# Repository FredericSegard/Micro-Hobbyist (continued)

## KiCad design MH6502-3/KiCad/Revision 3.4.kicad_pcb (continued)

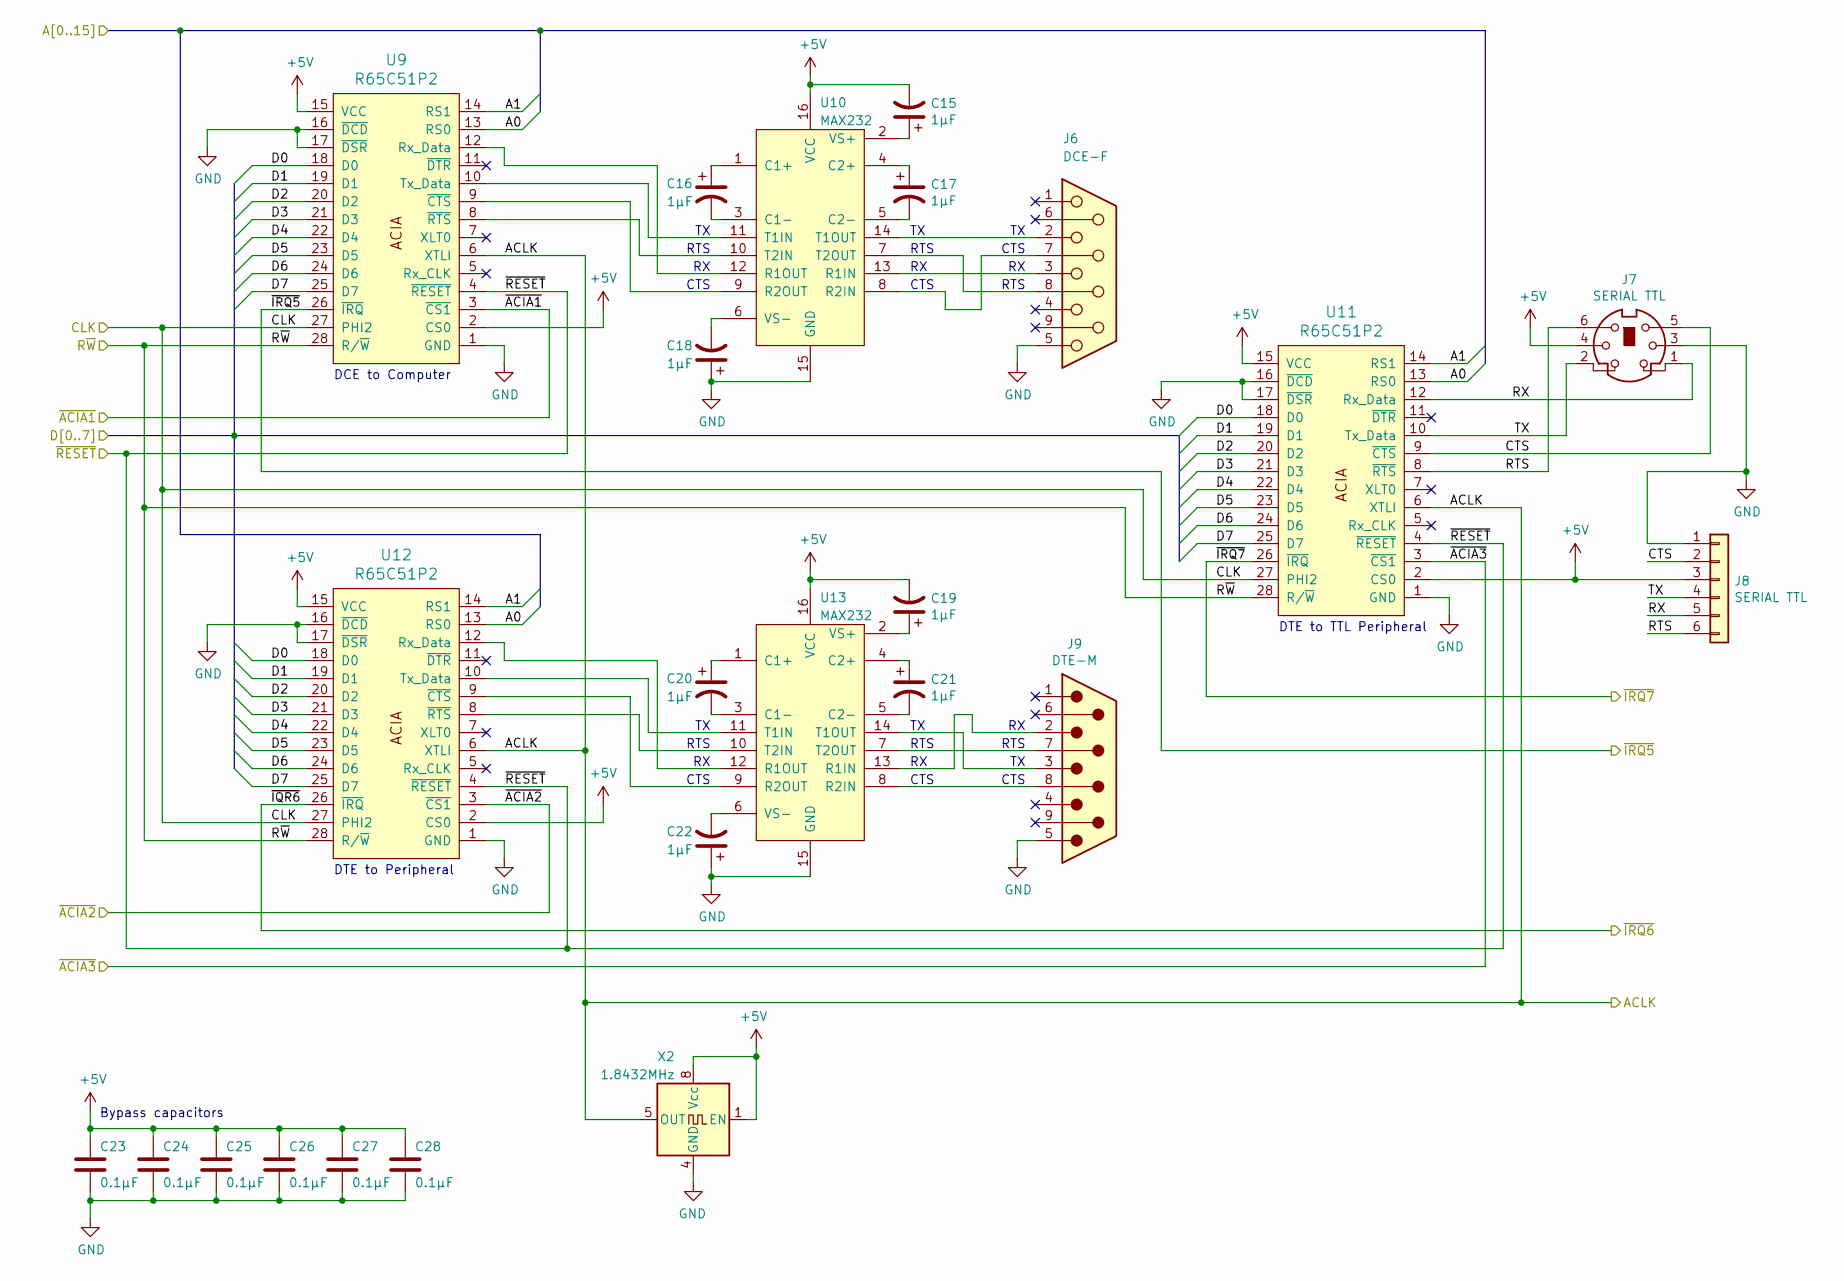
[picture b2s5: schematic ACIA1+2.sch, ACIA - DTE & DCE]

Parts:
C15, C16, C17, C18, C19, C20, C21, C22: 1µF; C_Disc_D3.0mm_W1.6mm_P2.50mm
C23, C24, C25, C26, C27, C28: 0.1µF; C_Disc_D3.0mm_W1.6mm_P2.50mm
J6: DCE-F; DSUB-9_Female_Horizontal_P2.77x2.84mm_EdgePinOffset7.70mm_H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
J7: SERIAL TTL; Mini-DIN_6p
J8: SERIAL TTL; PinHeader_1x06_P2.54mm_Vertical
J9: DTE-M; DSUB-9_Male_Horizontal_P2.77x2.84mm_EdgePinOffset7.70mm_Hou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
U9, U11, U12: R65C51P2; DIP-28_W15.24mm_Socket
U10, U13: MAX232; DIP-16_W7.62mm_Socket
X2: 1.8432MHz; Oscillator_DIP-8

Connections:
+5V: C15.2, C19.2, C23.1, C24.1, C25.1, C26.1, C27.1, C28.1, J7.4, J8.3, U9.2 (CS0), U9.15 (VCC), U10.16 (VCC), U11.2 (CS0), U11.15 (VCC), U12.2 (CS0), U12.15 (VCC), U13.16 (VCC), X2.1 (EN), X2.8 (Vcc); also elsewhere on the board
/ACIA 1, 2 & 3/A0: U9.13 (RS0), U11.13 (RS0), U12.13 (RS0); also elsewhere on the board
/ACIA 1, 2 & 3/A1: U9.14 (RS1), U11.14 (RS1), U12.14 (RS1); also elsewhere on the board
/ACIA 1, 2 & 3/CTS: J7.5, J8.2, U11.9 (~CTS)
/ACIA 1, 2 & 3/D0: U9.18 (D0), U11.18 (D0), U12.18 (D0); also elsewhere on the board
/ACIA 1, 2 & 3/D1: U9.19 (D1), U11.19 (D1), U12.19 (D1); also elsewhere on the board
/ACIA 1, 2 & 3/D2: U9.20 (D2), U11.20 (D2), U12.20 (D2); also elsewhere on the board
/ACIA 1, 2 & 3/D3: U9.21 (D3), U11.21 (D3), U12.21 (D3); also elsewhere on the board
/ACIA 1, 2 & 3/D4: U9.22 (D4), U11.22 (D4), U12.22 (D4); also elsewhere on the board
/ACIA 1, 2 & 3/D5: U9.23 (D5), U11.23 (D5), U12.23 (D5); also elsewhere on the board
/ACIA 1, 2 & 3/D6: U9.24 (D6), U11.24 (D6), U12.24 (D6); also elsewhere on the board
/ACIA 1, 2 & 3/D7: U9.25 (D7), U11.25 (D7), U12.25 (D7); also elsewhere on the board
/ACIA 1, 2 & 3/RTS: J7.6, J8.6, U11.8 (~RTS)
/ACIA 1, 2 & 3/RX: J7.1, J8.5, U11.12 (Rx_Data)
/ACIA 1, 2 & 3/TX: J7.2, J8.4, U11.10 (Tx_Data)
/ACLK: U9.6 (XTLI), U11.6 (XTLI), U12.6 (XTLI), X2.5 (OUT); also elsewhere on the board
/CLK: U9.27 (PHI2), U11.27 (PHI2), U12.27 (PHI2); also elsewhere on the board
/R~W: U9.28 (R/~W), U11.28 (R/~W), U12.28 (R/~W); also elsewhere on the board
/~ACIA1: U9.3 (~CS1); also elsewhere on the board
/~ACIA2: U12.3 (~CS1); also elsewhere on the board
/~ACIA3: U11.3 (~CS1); also elsewhere on the board
/~IRQ5: U9.26 (~IRQ); also elsewhere on the board
/~IRQ6: U12.26 (~IRQ); also elsewhere on the board
/~IRQ7: U11.26 (~IRQ); also elsewhere on the board
/~RESET: U9.4 (~RESET), U11.4 (~RESET), U12.4 (~RESET); also elsewhere on the board
GND: C18.1, C22.1, C23.2, C24.2, C25.2, C26.2, C27.2, C28.2, J6.5, J7.3, J8.1, J9.5, U9.1 (GND), U9.16 (~DCD), U9.17 (~DSR), U10.15 (GND), U11.1 (GND), U11.16 (~DCD), U11.17 (~DSR), U12.1 (GND), U12.16 (~DCD), U12.17 (~DSR), U13.15 (GND), X2.4 (GND); also elsewhere on the board
unnamed: C15.1, U10.2 (VS+)
unnamed: C16.1, U10.1 (C1+)
unnamed: C16.2, U10.3 (C1-)
unnamed: C17.1, U10.4 (C2+)
unnamed: C17.2, U10.5 (C2-)
unnamed: C18.2, U10.6 (VS-)
unnamed: C19.1, U13.2 (VS+)
unnamed: C20.1, U13.1 (C1+)
unnamed: C20.2, U13.3 (C1-)
unnamed: C21.1, U13.4 (C2+)
unnamed: C21.2, U13.5 (C2-)
unnamed: C22.2, U13.6 (VS-)
unnamed: J6.2, U10.14 (T1OUT)
unnamed: J6.3, U10.13 (R1IN)
unnamed: J6.7, U10.8 (R2IN)
unnamed: J6.8, U10.7 (T2OUT)
unnamed: J9.2, U13.13 (R1IN)
unnamed: J9.3, U13.14 (T1OUT)
unnamed: J9.7, U13.7 (T2OUT)
unnamed: J9.8, U13.8 (R2IN)
unnamed: U9.9 (~CTS), U10.9 (R2OUT)
unnamed: U9.8 (~RTS), U10.10 (T2IN)
unnamed: U9.10 (Tx_Data), U10.11 (T1IN)
unnamed: U9.12 (Rx_Data), U10.12 (R1OUT)
unnamed: U12.8 (~RTS), U13.10 (T2IN)
unnamed: U12.9 (~CTS), U13.9 (R2OUT)
unnamed: U12.10 (Tx_Data), U13.11 (T1IN)
unnamed: U12.12 (Rx_Data), U13.12 (R1OUT)

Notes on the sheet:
RTS
CTS
DCE to Computer
DTE to Peripheral
Bypass capacitors
DTE to TTL Peripheral

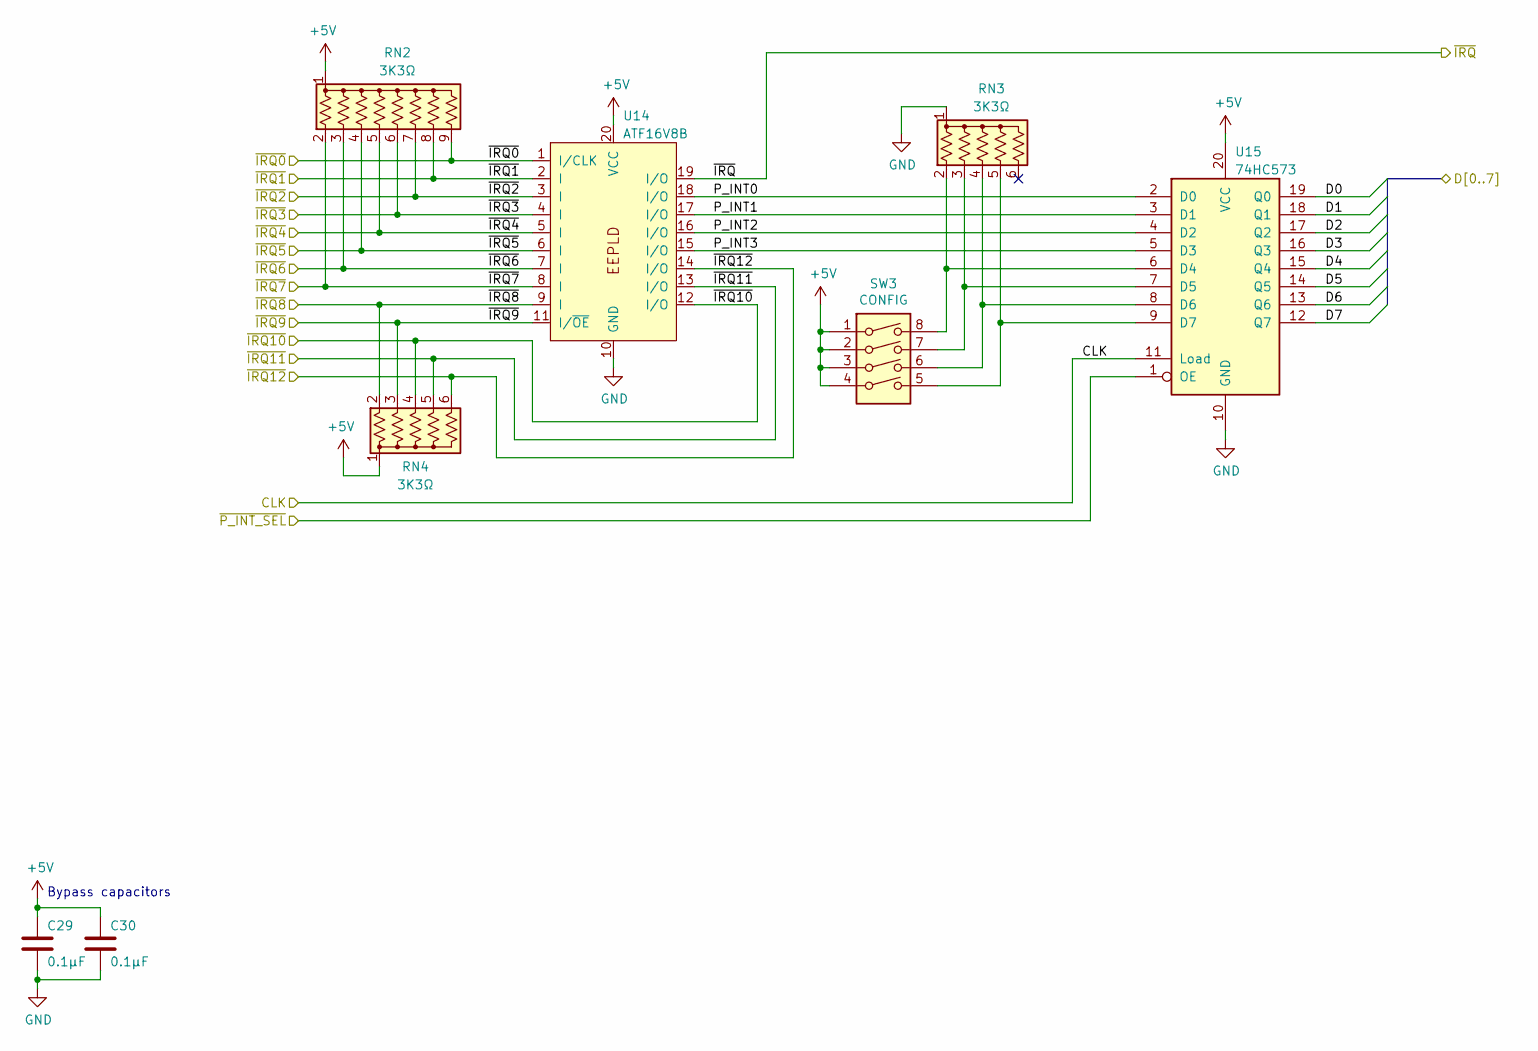
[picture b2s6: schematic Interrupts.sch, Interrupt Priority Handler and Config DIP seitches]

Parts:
C29, C30: 0.1µF; C_Disc_D3.0mm_W1.6mm_P2.50mm
RN2: 3K3Ω; R_Array_SIP9
RN3, RN4: 3K3Ω; R_Array_SIP6
SW3: CONFIG; SW_DIP_SPSTx04_Slide_9.78x12.34mm_W7.62mm_P2.54mm
U14: ATF16V8B; DIP-20_W7.62mm_Socket
U15: 74HC573; DIP-20_W7.62mm_Socket

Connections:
+5V: C29.1, C30.1, RN2.1 (common), RN4.1 (common), SW3.1, SW3.2, SW3.3, SW3.4, U14.20 (VCC), U15.20 (VCC); also elsewhere on the board
/ACIA 1, 2 & 3/D0: U15.19 (Q0); also elsewhere on the board
/ACIA 1, 2 & 3/D1: U15.18 (Q1); also elsewhere on the board
/ACIA 1, 2 & 3/D2: U15.17 (Q2); also elsewhere on the board
/ACIA 1, 2 & 3/D3: U15.16 (Q3); also elsewhere on the board
/ACIA 1, 2 & 3/D4: U15.15 (Q4); also elsewhere on the board
/ACIA 1, 2 & 3/D5: U15.14 (Q5); also elsewhere on the board
/ACIA 1, 2 & 3/D6: U15.13 (Q6); also elsewhere on the board
/ACIA 1, 2 & 3/D7: U15.12 (Q7); also elsewhere on the board
/CLK: U15.11 (Load); also elsewhere on the board
/Interrupt Handling/P_INT0: U14.18 (I/O), U15.2 (D0)
/Interrupt Handling/P_INT1: U14.17 (I/O), U15.3 (D1)
/Interrupt Handling/P_INT2: U14.16 (I/O), U15.4 (D2)
/Interrupt Handling/P_INT3: U14.15 (I/O), U15.5 (D3)
/~IRQ: U14.19 (I/O); also elsewhere on the board
/~IRQ0: RN2.9 (R8), U14.1 (I/CLK); also elsewhere on the board
/~IRQ1: RN2.8 (R7), U14.2 (I); also elsewhere on the board
/~IRQ2: RN2.7 (R6), U14.3 (I); also elsewhere on the board
/~IRQ3: RN2.6 (R5), U14.4 (I); also elsewhere on the board
/~IRQ4: RN2.5 (R4), U14.5 (I); also elsewhere on the board
/~IRQ5: RN2.4 (R3), U14.6 (I); also elsewhere on the board
/~IRQ6: RN2.3 (R2), U14.7 (I); also elsewhere on the board
/~IRQ7: RN2.2 (R1), U14.8 (I); also elsewhere on the board
/~IRQ8: RN4.2 (R1), U14.9 (I); also elsewhere on the board
/~IRQ9: RN4.3 (R2), U14.11 (I/~OE); also elsewhere on the board
/~IRQ10: RN4.4 (R3), U14.12 (I/O); also elsewhere on the board
/~IRQ11: RN4.5 (R4), U14.13 (I/O); also elsewhere on the board
/~IRQ12: RN4.6 (R5), U14.14 (I/O); also elsewhere on the board
/~P_INT_SEL: U15.1 (OE); also elsewhere on the board
GND: C29.2, C30.2, RN3.1 (common), U14.10 (GND), U15.10 (GND); also elsewhere on the board
unnamed: RN3.2 (R1), SW3.8, U15.6 (D4)
unnamed: RN3.3 (R2), SW3.7, U15.7 (D5)
unnamed: RN3.4 (R3), SW3.6, U15.8 (D6)
unnamed: RN3.5 (R4), SW3.5, U15.9 (D7)

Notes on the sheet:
Bypass capacitors

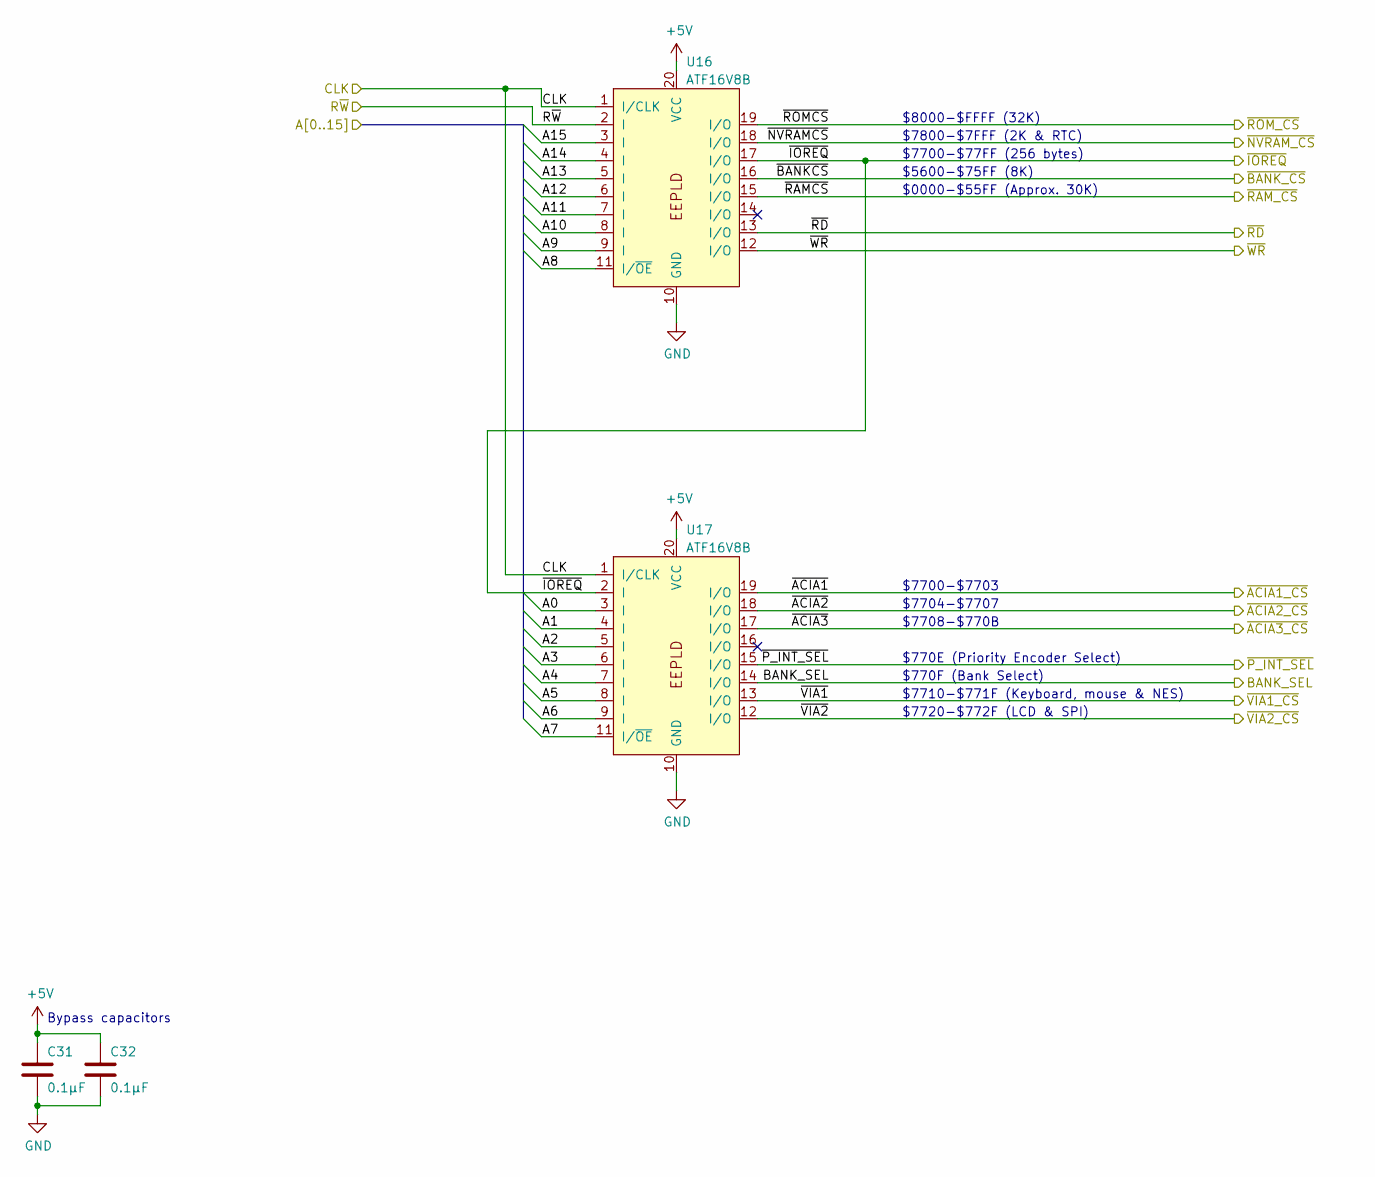
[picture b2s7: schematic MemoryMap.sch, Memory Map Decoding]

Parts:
C31, C32: 0.1µF; C_Disc_D3.0mm_W1.6mm_P2.50mm
U16, U17: ATF16V8B; DIP-20_W7.62mm_Socket

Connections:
+5V: C31.1, C32.1, U16.20 (VCC), U17.20 (VCC); also elsewhere on the board
/ACIA 1, 2 & 3/A0: U17.3 (I); also elsewhere on the board
/ACIA 1, 2 & 3/A1: U17.4 (I); also elsewhere on the board
/BANK_SEL: U17.14 (I/O); also elsewhere on the board
/Bus/A2: U17.5 (I); also elsewhere on the board
/Bus/A3: U17.6 (I); also elsewhere on the board
/Bus/A4: U17.7 (I); also elsewhere on the board
/Bus/A5: U17.8 (I); also elsewhere on the board
/Bus/A6: U17.9 (I); also elsewhere on the board
/Bus/A7: U17.11 (I/~OE); also elsewhere on the board
/Bus/A8: U16.11 (I/~OE); also elsewhere on the board
/Bus/A9: U16.9 (I); also elsewhere on the board
/Bus/A10: U16.8 (I); also elsewhere on the board
/Bus/A11: U16.7 (I); also elsewhere on the board
/Bus/A12: U16.6 (I); also elsewhere on the board
/Bus/A13: U16.5 (I); also elsewhere on the board
/Bus/A14: U16.4 (I); also elsewhere on the board
/Bus/A15: U16.3 (I); also elsewhere on the board
/CLK: U16.1 (I/CLK), U17.1 (I/CLK); also elsewhere on the board
/R~W: U16.2 (I); also elsewhere on the board
/~ACIA1: U17.19 (I/O); also elsewhere on the board
/~ACIA2: U17.18 (I/O); also elsewhere on the board
/~ACIA3: U17.17 (I/O); also elsewhere on the board
/~BANK: U16.16 (I/O); also elsewhere on the board
/~IOREQ: U16.17 (I/O), U17.2 (I); also elsewhere on the board
/~NVRAM: U16.18 (I/O); also elsewhere on the board
/~P_INT_SEL: U17.15 (I/O); also elsewhere on the board
/~RAM: U16.15 (I/O); also elsewhere on the board
/~RD: U16.13 (I/O); also elsewhere on the board
/~ROM: U16.19 (I/O); also elsewhere on the board
/~VIA1: U17.13 (I/O); also elsewhere on the board
/~VIA2: U17.12 (I/O); also elsewhere on the board
/~WR: U16.12 (I/O); also elsewhere on the board
GND: C31.2, C32.2, U16.10 (GND), U17.10 (GND); also elsewhere on the board

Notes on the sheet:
Bypass capacitors
$8000-$FFFF (32K)
$7800-$7FFF (2K & RTC)
$7700-$77FF (256 bytes)
$0000-$55FF (Approx. 30K)
$7700-$7703
$7704-$7707
$7708-$770B
$7710-$771F (Keyboard, mouse & NES)
$5600-$75FF (8K)
$770E (Priority Encoder Select)
$770F (Bank Select)
$7720-$772F (LCD & SPI)

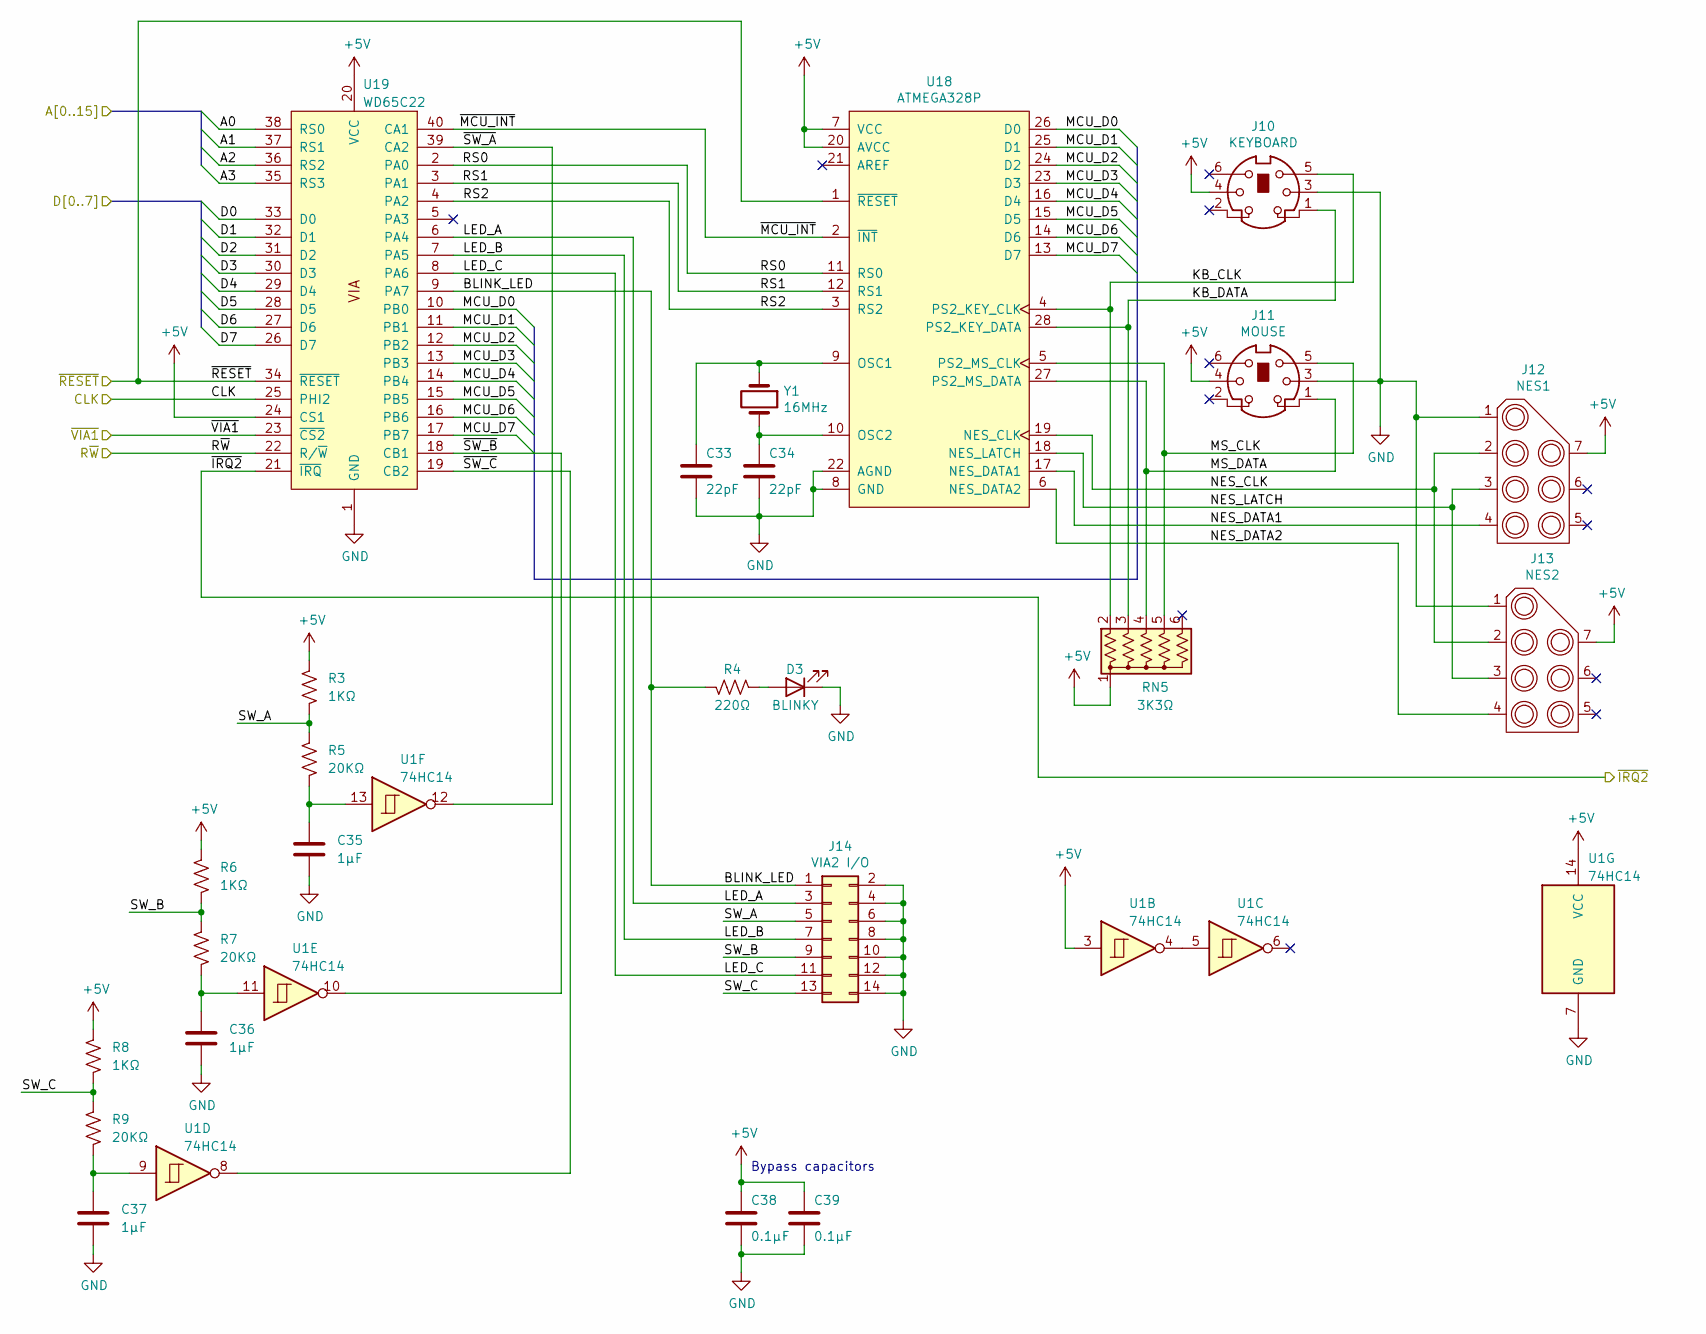
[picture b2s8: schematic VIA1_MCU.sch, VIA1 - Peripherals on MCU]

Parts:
C33, C34: 22pF; C_Disc_D3.0mm_W1.6mm_P2.50mm
C35, C36, C37: 1µF; C_Disc_D3.0mm_W1.6mm_P2.50mm
C38, C39: 0.1µF; C_Disc_D3.0mm_W1.6mm_P2.50mm
D3: BLINKY; LED_D3.0mm
J10: KEYBOARD; Mini-DIN_6p
J11: MOUSE; Mini-DIN_6p
J12: NES1; NES_Connector
J13: NES2; NES_Connector
J14: VIA2 I/O; PinHeader_2x07_P2.54mm_Vertical
R3, R6, R8: 1KΩ; R_Axial_DIN0207_L6.3mm_D2.5mm_P10.16mm_Horizontal
R4: 220Ω; R_Axial_DIN0207_L6.3mm_D2.5mm_P10.16mm_Horizontal
R5, R7, R9: 20KΩ; R_Axial_DIN0207_L6.3mm_D2.5mm_P10.16mm_Horizontal
RN5: 3K3Ω; R_Array_SIP6
U1: 74HC14; DIP-14_W7.62mm_Socket
U18: ATMEGA328P; DIP-28_W7.62mm_Socket
U19: WD65C22; DIP-40_W15.24mm_Socket
Y1: 16MHz; Crystal_HC18-U_Vertical

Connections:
+5V: C38.1, C39.1, J10.4, J11.4, J12.7, J13.7, R3.2, R6.2, R8.2, RN5.1 (common), U1.3, U1.14 (VCC), U18.7 (VCC), U18.20 (AVCC), U19.20 (VCC), U19.24 (CS1); also elsewhere on the board
/ACIA 1, 2 & 3/A0: U19.38 (RS0); also elsewhere on the board
/ACIA 1, 2 & 3/A1: U19.37 (RS1); also elsewhere on the board
/ACIA 1, 2 & 3/D0: U19.33 (D0); also elsewhere on the board
/ACIA 1, 2 & 3/D1: U19.32 (D1); also elsewhere on the board
/ACIA 1, 2 & 3/D2: U19.31 (D2); also elsewhere on the board
/ACIA 1, 2 & 3/D3: U19.30 (D3); also elsewhere on the board
/ACIA 1, 2 & 3/D4: U19.29 (D4); also elsewhere on the board
/ACIA 1, 2 & 3/D5: U19.28 (D5); also elsewhere on the board
/ACIA 1, 2 & 3/D6: U19.27 (D6); also elsewhere on the board
/ACIA 1, 2 & 3/D7: U19.26 (D7); also elsewhere on the board
/Bus/A2: U19.36 (RS2); also elsewhere on the board
/Bus/A3: U19.35 (RS3); also elsewhere on the board
/CLK: U19.25 (PHI2); also elsewhere on the board
/R~W: U19.22 (R/~W); also elsewhere on the board
/VIA1 - Peripherals/BLINK_LED: J14.1, R4.2, U19.9 (PA7)
/VIA1 - Peripherals/KB_CLK: J10.5, RN5.2 (R1), U18.4 (PS2_KEY_CLK)
/VIA1 - Peripherals/KB_DATA: J10.1, RN5.3 (R2), U18.28 (PS2_KEY_DATA)
/VIA1 - Peripherals/LED_A: J14.3, U19.6 (PA4)
/VIA1 - Peripherals/LED_B: J14.7, U19.7 (PA5)
/VIA1 - Peripherals/LED_C: J14.11, U19.8 (PA6)
/VIA1 - Peripherals/MCU_D0: U18.26 (D0), U19.10 (PB0)
/VIA1 - Peripherals/MCU_D1: U18.25 (D1), U19.11 (PB1)
/VIA1 - Peripherals/MCU_D2: U18.24 (D2), U19.12 (PB2)
/VIA1 - Peripherals/MCU_D3: U18.23 (D3), U19.13 (PB3)
/VIA1 - Peripherals/MCU_D4: U18.16 (D4), U19.14 (PB4)
/VIA1 - Peripherals/MCU_D5: U18.15 (D5), U19.15 (PB5)
/VIA1 - Peripherals/MCU_D6: U18.14 (D6), U19.16 (PB6)
/VIA1 - Peripherals/MCU_D7: U18.13 (D7), U19.17 (PB7)
/VIA1 - Peripherals/MS_CLK: J11.5, RN5.5 (R4), U18.5 (PS2_MS_CLK)
/VIA1 - Peripherals/MS_DATA: J11.1, RN5.4 (R3), U18.27 (PS2_MS_DATA)
/VIA1 - Peripherals/NES_CLK: J12.2, J13.2, U18.19 (NES_CLK)
/VIA1 - Peripherals/NES_DATA1: J12.4, U18.17 (NES_DATA1)
/VIA1 - Peripherals/NES_DATA2: J13.4, U18.6 (NES_DATA2)
/VIA1 - Peripherals/NES_LATCH: J12.3, J13.3, U18.18 (NES_LATCH)
/VIA1 - Peripherals/RS0: U18.11 (RS0), U19.2 (PA0)
/VIA1 - Peripherals/RS1: U18.12 (RS1), U19.3 (PA1)
/VIA1 - Peripherals/RS2: U18.3 (RS2), U19.4 (PA2)
/VIA1 - Peripherals/SW_A: J14.5, R3.1, R5.2
/VIA1 - Peripherals/SW_B: J14.9, R6.1, R7.2
/VIA1 - Peripherals/SW_C: J14.13, R8.1, R9.2
/VIA1 - Peripherals/~MCU_INT: U18.2 (~INT), U19.40 (CA1)
/VIA1 - Peripherals/~SW_A: U1.12, U19.39 (CA2)
/VIA1 - Peripherals/~SW_B: U1.10, U19.18 (CB1)
/VIA1 - Peripherals/~SW_C: U1.8, U19.19 (CB2)
/~IRQ2: U19.21 (~IRQ); also elsewhere on the board
/~RESET: U18.1 (~RESET), U19.34 (~RESET); also elsewhere on the board
/~VIA1: U19.23 (~CS2); also elsewhere on the board
GND: C33.2, C34.2, C35.2, C36.2, C37.2, C38.2, C39.2, D3.1 (K), J10.3, J11.3, J12.1, J13.1, J14.2, J14.4, J14.6, J14.8, J14.10, J14.12, J14.14, U1.7 (GND), U18.8 (GND), U18.22 (AGND), U19.1 (GND); also elsewhere on the board
unnamed: C33.1, U18.9 (OSC1), Y1.1
unnamed: C34.1, U18.10 (OSC2), Y1.2
unnamed: C35.1, R5.1, U1.13
unnamed: C36.1, R7.1, U1.11
unnamed: C37.1, R9.1, U1.9
unnamed: D3.2 (A), R4.1
unnamed: U1.4, U1.5

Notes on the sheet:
Bypass capacitors

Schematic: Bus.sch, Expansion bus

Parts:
C40, C41, C42, C43: 10µF; CP_Radial_D6.3mm_P2.50mm
J15: BB BUS; PinHeader_2x20_P2.54mm_Vertical
J16, J18: PWR; PinSocket_2x03_P2.54mm_Vertical
J17: EXT BUS; PinHeader_2x32_P2.54mm_Vertical

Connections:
+5V: C40.1, C41.1, C42.1, C43.1, J15.2, J15.4, J15.37, J15.39, J16.1, J16.3, J16.5, J17.2, J17.4, J17.61, J17.63, J18.1, J18.3, J18.5; also elsewhere on the board
/ACIA 1, 2 & 3/A0: J15.13, J17.13; also elsewhere on the board
/ACIA 1, 2 & 3/A1: J15.14, J17.14; also elsewhere on the board
/ACIA 1, 2 & 3/D0: J15.5, J17.5; also elsewhere on the board
/ACIA 1, 2 & 3/D1: J15.6, J17.6; also elsewhere on the board
/ACIA 1, 2 & 3/D2: J15.7, J17.7; also elsewhere on the board
/ACIA 1, 2 & 3/D3: J15.8, J17.8; also elsewhere on the board
/ACIA 1, 2 & 3/D4: J15.9, J17.9; also elsewhere on the board
/ACIA 1, 2 & 3/D5: J15.10, J17.10; also elsewhere on the board
/ACIA 1, 2 & 3/D6: J15.11, J17.11; also elsewhere on the board
/ACIA 1, 2 & 3/D7: J15.12, J17.12; also elsewhere on the board
/ACLK: J15.33, J17.47; also elsewhere on the board
/BE: J17.51; also elsewhere on the board
/Bus/A2: J15.15, J17.15; also elsewhere on the board
/Bus/A3: J15.16, J17.16; also elsewhere on the board
/Bus/A4: J15.17, J17.17; also elsewhere on the board
/Bus/A5: J15.18, J17.18; also elsewhere on the board
/Bus/A6: J15.19, J17.19; also elsewhere on the board
/Bus/A7: J15.20, J17.20; also elsewhere on the board
/Bus/A8: J17.21; also elsewhere on the board
/Bus/A9: J17.22; also elsewhere on the board
/Bus/A10: J17.23; also elsewhere on the board
/Bus/A11: J17.24; also elsewhere on the board
/Bus/A12: J17.25; also elsewhere on the board
/Bus/A13: J17.26; also elsewhere on the board
/Bus/A14: J17.27; also elsewhere on the board
/Bus/A15: J17.28; also elsewhere on the board
/CLK: J15.23, J17.31; also elsewhere on the board
/HCLK: J15.34, J17.48; also elsewhere on the board
/RDY: J15.35, J17.49; also elsewhere on the board
/R~W: J15.25, J17.33; also elsewhere on the board
/SYNC: J15.36, J17.50; also elsewhere on the board
/~CLK: J15.24, J17.32; also elsewhere on the board
/~IOREQ: J15.21, J17.29; also elsewhere on the board
/~IRQ0: J15.29, J17.37; also elsewhere on the board
/~IRQ1: J15.30, J17.38; also elsewhere on the board
/~IRQ3: J17.39; also elsewhere on the board
/~IRQ4: J17.40; also elsewhere on the board
/~IRQ8: J15.31, J17.41; also elsewhere on the board
/~IRQ9: J15.32, J17.42; also elsewhere on the board
/~IRQ10: J17.43; also elsewhere on the board
/~IRQ11: J17.44; also elsewhere on the board
/~ML: J17.52; also elsewhere on the board
/~NMI: J15.28, J17.36; also elsewhere on the board
/~RD: J15.26, J17.34; also elsewhere on the board
/~RESET: J15.22, J17.30; also elsewhere on the board
/~VP: J17.53; also elsewhere on the board
/~WR: J15.27, J17.35; also elsewhere on the board
GND: C40.2, C41.2, C42.2, C43.2, J15.1, J15.3, J15.38, J15.40, J16.2, J16.4, J16.6, J17.1, J17.3, J17.62, J17.64, J18.2, J18.4, J18.6; also elsewhere on the board

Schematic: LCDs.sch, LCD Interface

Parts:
C44: 0.1µF; C_Disc_D3.0mm_W1.6mm_P2.50mm
C45, C46: 1µF; CP_Radial_D5.0mm_P2.50mm
J19: VIA2 I/O; PinHeader_2x03_P2.54mm_Vertical
J20: LCD; PinHeader_1x20_P2.54mm_Vertical
J21: LCD TYPE 15; PinHeader_1x03_P2.54mm_Vertical
J22: LCD TYPE 16; PinHeader_1x03_P2.54mm_Vertical
R10, R11, R12: 3K3Ω; R_Axial_DIN0207_L6.3mm_D2.5mm_P10.16mm_Horizontal
RV1: CONTRAST; Potentiometer_Bourns_3296W_Vertical
U20: WD65C22; DIP-40_W15.24mm_Socket

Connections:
+5V: C44.1, C45.1, C46.1, J19.2, J19.4, J19.6, J20.2, J20.19, J21.3, RV1.1, U20.20 (VCC), U20.24 (CS1); also elsewhere on the board
/ACIA 1, 2 & 3/A0: U20.38 (RS0); also elsewhere on the board
/ACIA 1, 2 & 3/A1: U20.37 (RS1); also elsewhere on the board
/ACIA 1, 2 & 3/D0: U20.33 (D0); also elsewhere on the board
/ACIA 1, 2 & 3/D1: U20.32 (D1); also elsewhere on the board
/ACIA 1, 2 & 3/D2: U20.31 (D2); also elsewhere on the board
/ACIA 1, 2 & 3/D3: U20.30 (D3); also elsewhere on the board
/ACIA 1, 2 & 3/D4: U20.29 (D4); also elsewhere on the board
/ACIA 1, 2 & 3/D5: U20.28 (D5); also elsewhere on the board
/ACIA 1, 2 & 3/D6: U20.27 (D6); also elsewhere on the board
/ACIA 1, 2 & 3/D7: U20.26 (D7); also elsewhere on the board
/Bus/A2: U20.36 (RS2); also elsewhere on the board
/Bus/A3: U20.35 (RS3); also elsewhere on the board
/CLK: U20.25 (PHI2); also elsewhere on the board
/LCD/BA: J19.1, R10.1, U20.2 (PA0)
/LCD/BB: J19.3, R11.1, U20.3 (PA1)
/LCD/BC: J19.5, R12.1, U20.4 (PA2)
/LCD/CS1: J21.1, U20.5 (PA3)
/LCD/CS1_5V: J20.15, J21.2
/LCD/CS2: J22.1, U20.6 (PA4)
/LCD/CS2_GND: J20.16, J22.2
/LCD/DB0: J20.7, U20.10 (PB0)
/LCD/DB1: J20.8, U20.11 (PB1)
/LCD/DB2: J20.9, U20.12 (PB2)
/LCD/DB3: J20.10, U20.13 (PB3)
/LCD/DB4: J20.11, U20.14 (PB4)
/LCD/DB5: J20.12, U20.15 (PB5)
/LCD/DB6: J20.13, U20.16 (PB6)
/LCD/DB7: J20.14, U20.17 (PB7)
/LCD/D~I: J20.4, U20.7 (PA5)
/LCD/E: J20.6, U20.9 (PA7)
/LCD/VO: J20.3, RV1.2
/R~W: J20.5, U20.8 (PA6), U20.22 (R/~W); also elsewhere on the board
/~IRQ12: U20.21 (~IRQ); also elsewhere on the board
/~RESET: J20.17, U20.34 (~RESET); also elsewhere on the board
/~VIA2: U20.23 (~CS2); also elsewhere on the board
GND: C44.2, C45.2, C46.2, J20.1, J20.20, J22.3, R10.2, R11.2, R12.2, RV1.3, U20.1 (GND); also elsewhere on the board

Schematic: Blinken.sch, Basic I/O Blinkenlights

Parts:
C47: 0.1µF; C_Disc_D3.0mm_W1.6mm_P2.50mm
D4: ACIA1; LED_D3.0mm
D5: ACIA2; LED_D3.0mm
D6: ACIA3; LED_D3.0mm
D7: VIA1; LED_D3.0mm
D8: VIA2; LED_D3.0mm
D9: IRQ; LED_D3.0mm
D10: NMI; LED_D3.0mm
RN6: 330Ω; R_Array_SIP9
U21: 74HC563; DIP-20_W7.62mm_Socket

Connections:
+5V: C47.1, U21.20 (VCC); also elsewhere on the board
/CLK: U21.11 (LE); also elsewhere on the board
/~ACIA1: U21.2 (D0); also elsewhere on the board
/~ACIA2: U21.3 (D1); also elsewhere on the board
/~ACIA3: U21.4 (D2); also elsewhere on the board
/~IRQ: U21.7 (D5); also elsewhere on the board
/~NMI: U21.8 (D6); also elsewhere on the board
/~VIA1: U21.5 (D3); also elsewhere on the board
/~VIA2: U21.6 (D4); also elsewhere on the board
GND: C47.2, RN6.1 (common), U21.1 (OE), U21.9 (D7), U21.10 (GND); also elsewhere on the board
unnamed: D4.1 (K), RN6.2 (R1)
unnamed: D4.2 (A), U21.19 (Q0)
unnamed: D5.1 (K), RN6.3 (R2)
unnamed: D5.2 (A), U21.18 (Q1)
unnamed: D6.1 (K), RN6.4 (R3)
unnamed: D6.2 (A), U21.17 (Q2)
unnamed: D7.1 (K), RN6.5 (R4)
unnamed: D7.2 (A), U21.16 (Q3)
unnamed: D8.1 (K), RN6.6 (R5)
unnamed: D8.2 (A), U21.15 (Q4)
unnamed: D9.1 (K), RN6.7 (R6)
unnamed: D9.2 (A), U21.14 (Q5)
unnamed: D10.1 (K), RN6.8 (R7)
unnamed: D10.2 (A), U21.13 (Q6)

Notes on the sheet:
Bypass capacitor

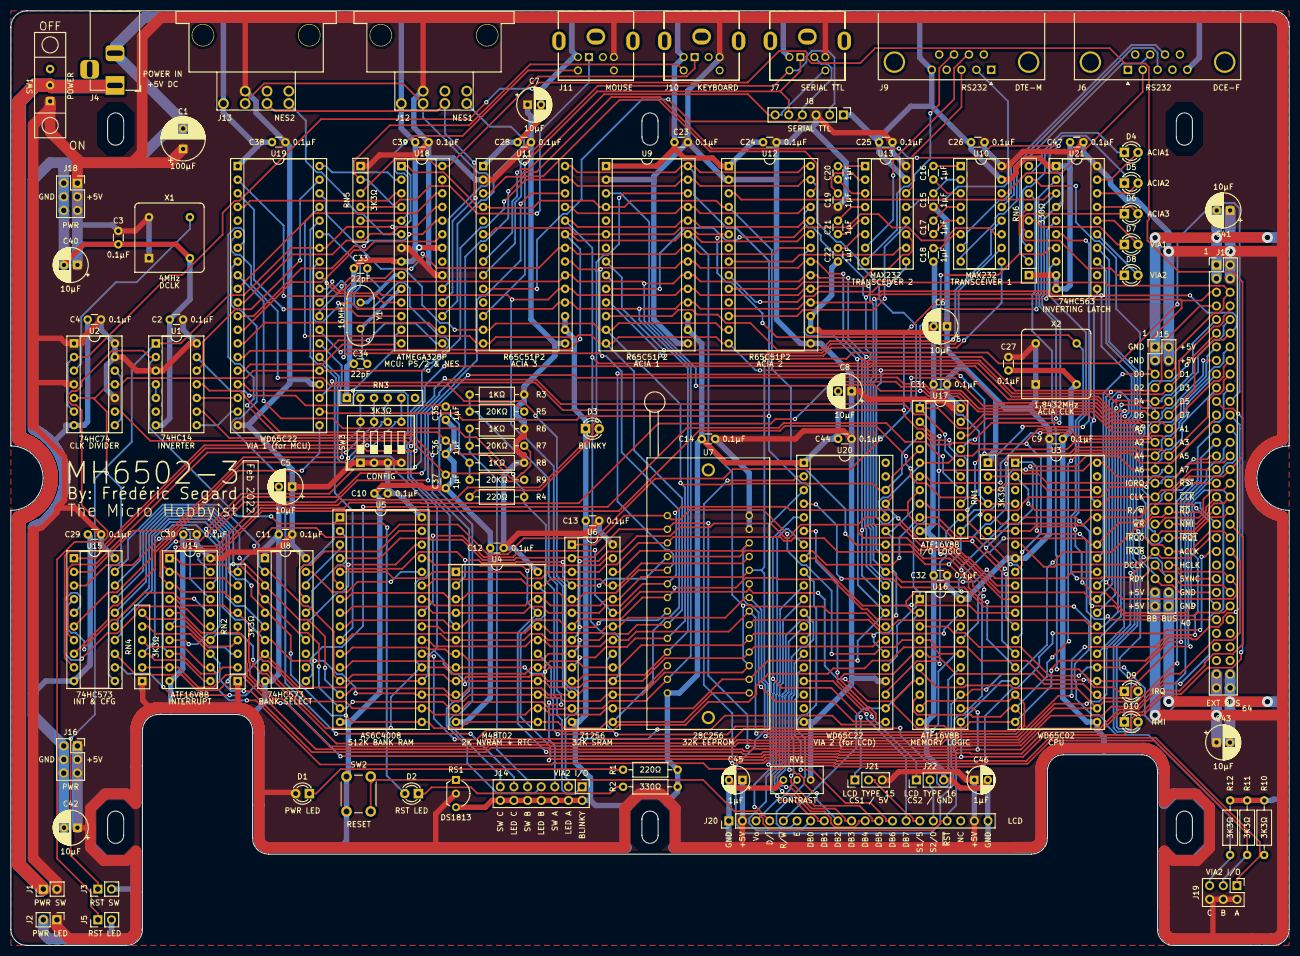
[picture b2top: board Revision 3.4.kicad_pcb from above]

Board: 2 copper layers, 238.0 x 174.0 mm, 126 parts (0 on the bottom side), 188 nets.

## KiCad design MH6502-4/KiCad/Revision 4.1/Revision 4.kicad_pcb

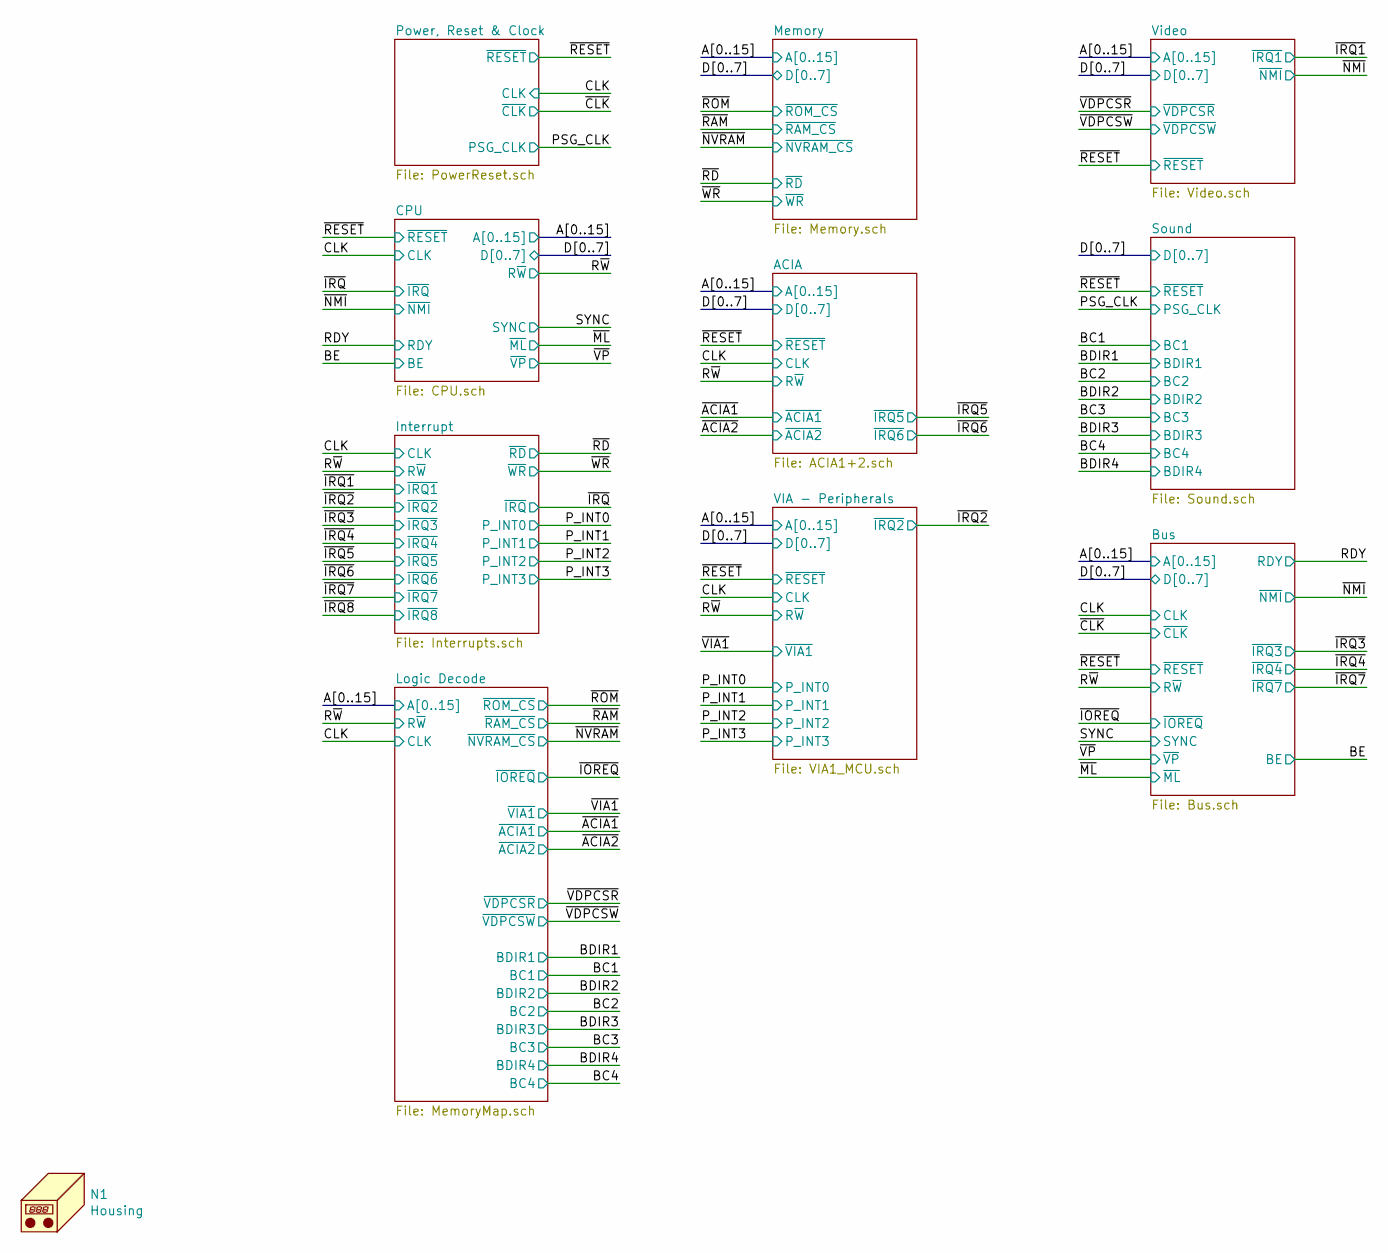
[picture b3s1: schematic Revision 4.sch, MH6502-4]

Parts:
N1: Housing; 18877_Housing
